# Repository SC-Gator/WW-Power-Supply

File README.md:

# WW-Power-Supply

Based on https://github.com/holmesrichards/ww_supply
and https://github.com/MyModularJourney/Octobus

Ultimately based on MFOS Wall Wart Supply http://musicfromouterspace.com/analogsynth_new/WALLWARTSUPPLY/WALLWARTSUPPLY.php

Revision - 3 (Built, Working)

* Modified layout to allow larger heatsinks
* (8) 10-pin Euro power connectors

Revision - 2 (Built, Working)

* 100mm x 99mm board for cost
* (4) 4700uF Caps instead of (6) 3300uF Caps
* DC jack and (2) 2-terminal connectors for 12VAC input and daisy chaining
* 3-terminal connector and (5) 10-pin Euro power connectors for output

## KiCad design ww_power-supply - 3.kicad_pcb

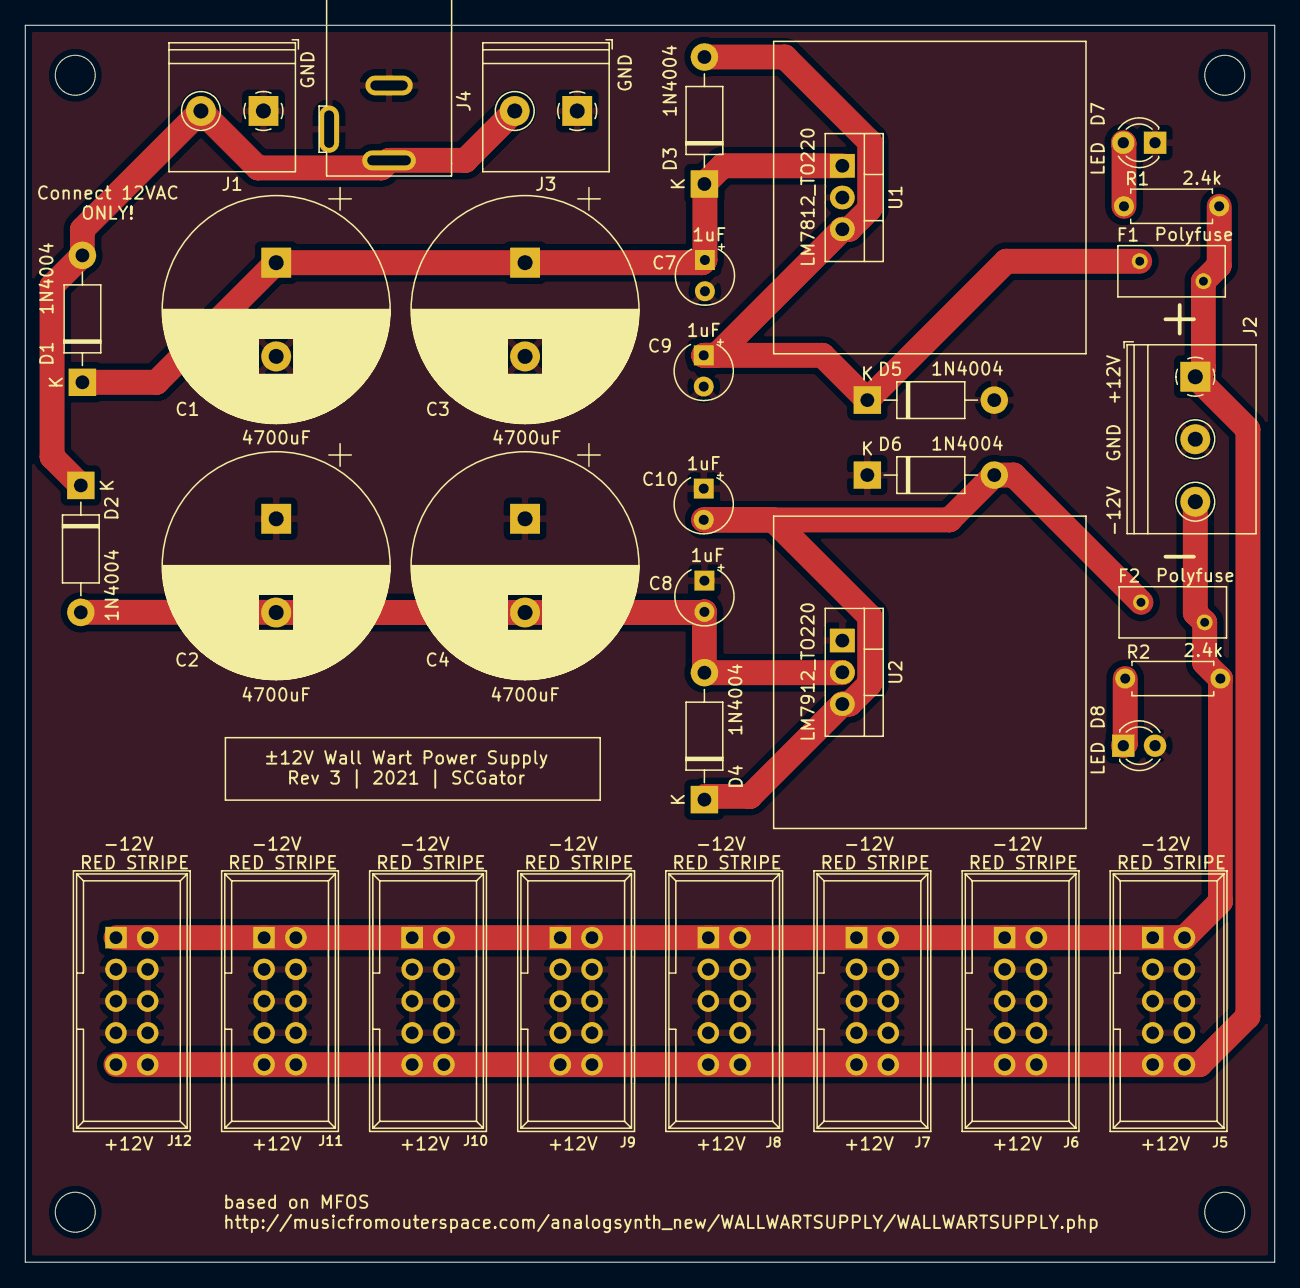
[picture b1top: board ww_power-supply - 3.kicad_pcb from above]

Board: 2 copper layers, 100.0 x 99.0 mm, 38 parts (0 on the bottom side), 10 nets.

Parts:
C1, C2, C3, C4: 4700uF; CP_Radial_D18.0mm_P7.50mm
C7, C8, C9, C10: 1uF; CP_Radial_Tantal_D4.5mm_P2.50mm
D1, D2, D3, D4, D5, D6: 1N4004; D_DO-41_SOD81_P10.16mm_Horizontal
D7, D8: LED; LED_D3.0mm
F1, F2: Polyfuse; Fuse_BelFuse_0ZRE0005FF_L8.3mm_W3.8mm
H1, H2, H3, H4: MountingHole; MountingHole_3.2mm_M3
J1, J3: Conn_01x02; TerminalBlock_Philmore_TB132_1x02_P5.00mm_Horizontal
J2: Conn_01x03; TerminalBlock_Philmore_TB133_1x03_P5.00mm_Horizontal
J4: Conn_01x03; Wall_wart_A-4118
J5, J6, J7, J8, J9, J10, J11, J12: EuroPwr; Power_Header
R1, R2: 2.4k; R_Axial_DIN0207_L6.3mm_D2.5mm_P7.62mm_Horizontal
U1: LM7812_TO220; TO-220-3_Vertical
U2: LM7912_TO220; TO-220-3_Vertical

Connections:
+12V: F1.1, J2.1, J5.9, J5.10, J6.9, J6.10, J7.9, J7.10, J8.9, J8.10, J9.9, J9.10, J10.9, J10.10, J11.9, J11.10, J12.9, J12.10, R1.2
-12V: F2.1, J2.3, J5.1, J5.2, J6.1, J6.2, J7.1, J7.2, J8.1, J8.2, J9.1, J9.2, J10.1, J10.2, J11.1, J11.2, J12.1, J12.2, R2.2
GND: C1.2, C2.1, C3.2, C4.1, C7.2, C8.1, C9.2, C10.1, D5.2, D6.1, D7.1, D8.2, J1.1, J2.2, J3.1, J4.1, J4.2, J5.3, J5.4, J5.5, J5.6, J5.7, J5.8, J6.3, J6.4, J6.5, J6.6, J6.7, J6.8, J7.3, J7.4, J7.5, J7.6, J7.7, J7.8, J8.3, J8.4, J8.5, J8.6, J8.7, J8.8, J9.3, J9.4, J9.5, J9.6, J9.7, J9.8, J10.3, J10.4, J10.5, J10.6, J10.7, J10.8, J11.3, J11.4, J11.5, J11.6, J11.7, J11.8, J12.3, J12.4, J12.5, J12.6, J12.7, J12.8, U1.2, U2.1
unnamed: C1.1, C3.1, C7.1, D1.1, D3.1, U1.1
unnamed: C2.2, C4.2, C8.2, D2.2, D4.2, U2.2
unnamed: C9.1, D3.2, D5.1, F1.2, U1.3
unnamed: C10.2, D4.1, D6.2, F2.2, U2.3
unnamed: D1.2, D2.1, J1.2, J3.2, J4.3
unnamed: D7.2, R1.1
unnamed: D8.1, R2.1
